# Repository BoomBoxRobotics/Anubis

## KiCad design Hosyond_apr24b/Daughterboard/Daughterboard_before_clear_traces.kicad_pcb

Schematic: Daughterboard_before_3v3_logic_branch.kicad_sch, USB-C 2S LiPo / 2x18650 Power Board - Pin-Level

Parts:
BT1: 18650 Cell 1 lower
BT2: 18650 Cell 2 upper
C1: 10uF 10V X5R; C_0805_2012Metric
C2, C8, C17, C19, C27, C29: 100nF 10V X7R; C_0603_1608Metric
C3, C5: 22uF 16V X5R; C_0805_2012Metric
C4, C7, C9, C10, C12, C15, C21, C24, C25, C26: 100nF 16V X7R; C_0603_1608Metric
C6: 4.7uF 6.3V X5R; C_0603_1608Metric
C11, C16: 10uF 16V X5R; C_0805_2012Metric
C13, C14, C22, C23: 22uF 10V X5R; C_0805_2012Metric
C18, C20, C28: 1uF 10V X5R; C_0603_1608Metric
D1: 5V VBUS TVS; D_SOD-323
D2: LED green; LED_0603_1608Metric
D3: LED blue; LED_0603_1608Metric
D4, D5, D6, D7: 4ch 3.3V GPIO TVS array TBD; SOT-23-6_NoPad6
F1: 2A hold polyfuse; Fuse_1206_3216Metric
F2: PTC/fuse cell1; Fuse_1206_3216Metric
F3: PTC/fuse cell2; Fuse_1206_3216Metric
F4: 2A system fuse; Fuse_1206_3216Metric
J1: USB-C 5V Sink; USB_C_Receptacle_GCT_USB4125-xx-x_6P_TopMnt_Horizontal
J2: Switched power outputs
J4: UART JST-GH 1.25mm; JST_GH_SM05B-GHS-TB_1x05-1MP_P1.25mm_Horizontal
J5: I2C male header 2.54mm; PinHeader_1x04_P2.54mm_Vertical
J6: Deep sleep pushbutton header; PinHeader_1x02_P2.54mm_Vertical
J7: 2S balance input JST-XH; JST_XH_B3B-XH-A_1x03_P2.50mm_Vertical
J8: Analog input header; PinHeader_1x10_P2.54mm_Vertical
J30: J3P Hosyond +5V_SW solder pad; TestPoint_Pad_1.5x1.5mm
J31: J3A Hosyond UART_TX solder pad; TestPoint_Pad_1.5x1.5mm
J32: J3B Hosyond UART_RX solder pad; TestPoint_Pad_1.5x1.5mm
J33: J3C Hosyond I2C_SDA solder pad; TestPoint_Pad_1.5x1.5mm
J34: J3D Hosyond I2C_SCL solder pad; TestPoint_Pad_1.5x1.5mm
J35: J3E Hosyond GPIO2 solder pad; TestPoint_Pad_1.5x1.5mm
J36: J3F Hosyond GPIO3 solder pad; TestPoint_Pad_1.5x1.5mm
J37: J3G Hosyond GPIO14 solder pad; TestPoint_Pad_1.5x1.5mm
J38: J3H Hosyond GPIO21 solder pad; TestPoint_Pad_1.5x1.5mm
J39: J3I Hosyond GND solder pad; TestPoint_Pad_1.5x1.5mm
J91: MCP23017 GPA0 solder pad; TestPoint_Pad_1.5x1.5mm
J92: MCP23017 GPA1 solder pad; TestPoint_Pad_1.5x1.5mm
J93: MCP23017 GPA2 solder pad; TestPoint_Pad_1.5x1.5mm
J94: MCP23017 GPA3 solder pad; TestPoint_Pad_1.5x1.5mm
J95: MCP23017 GPA4 solder pad; TestPoint_Pad_1.5x1.5mm
J96: MCP23017 GPA5 solder pad; TestPoint_Pad_1.5x1.5mm
J97: MCP23017 GPA6 solder pad; TestPoint_Pad_1.5x1.5mm
J98: MCP23017 GPA7 solder pad; TestPoint_Pad_1.5x1.5mm
J99: MCP23017 GPB0 solder pad; TestPoint_Pad_1.5x1.5mm
J910: MCP23017 GPB1 solder pad; TestPoint_Pad_1.5x1.5mm
J911: MCP23017 GPB2 solder pad; TestPoint_Pad_1.5x1.5mm
J912: MCP23017 GPB3 solder pad; TestPoint_Pad_1.5x1.5mm
J913: MCP23017 GPB4 solder pad; TestPoint_Pad_1.5x1.5mm
J914: MCP23017 GPB5 solder pad; TestPoint_Pad_1.5x1.5mm
J915: MCP23017 GPB6 solder pad; TestPoint_Pad_1.5x1.5mm
J916: MCP23017 GPB7 solder pad; TestPoint_Pad_1.5x1.5mm
J925: MCP23017 INTA solder pad; TestPoint_Pad_1.5x1.5mm
J926: MCP23017 INTB solder pad; TestPoint_Pad_1.5x1.5mm
J927: MCP23017 RESET solder pad; TestPoint_Pad_1.5x1.5mm
J928: MCP23017 +3V3_SW solder pad; TestPoint_Pad_1.5x1.5mm
J929: MCP23017 GND solder pad; TestPoint_Pad_1.5x1.5mm
L1: 4.7uH >=3A sat; L_APV_ANR4020
L2: 4.7uH >=2A sat; L_APV_ANR4020
L3: 1uH >=4A sat; L_APV_ANR5040
Q1: CSD83325L; CSD83325L_YJE0006A
R1, R2: 5.1k 1%; R_0603_1608Metric
R3: 806R 1% TBD; R_0603_1608Metric
R4: TBD 1%; R_0603_1608Metric
R5: 10k 1%; R_0603_1608Metric
R6, R7: 2.2k; R_0603_1608Metric
R8: 523k 1%; R_0603_1608Metric
R9, R12: 100k 1%; R_0603_1608Metric
R10, R13: 100k; R_0603_1608Metric
R11: 316k 1%; R_0603_1608Metric
R14, R15: 470R 1%; R_0603_1608Metric
R16: 2.0k 1%; R_0603_1608Metric
R17, R18: 330R; R_0603_1608Metric
R19, R20: 4.7k; R_0603_1608Metric
R21, R22, R23, R24, R25, R26, R27, R28, R29, R30, R31, R32, R33, R34, R35, R36, R37, R38: 100R; R_0603_1608Metric
R39, R40, R41: 0R; R_0603_1608Metric
R42, R43, R44: 10k; R_0603_1608Metric
SW1: Pololu #2808 5V switch; Pololu_2808_Raised_Header
SW2: Pololu #2808 3V3 switch; Pololu_2808_Raised_Header
TH1: 10k NTC; R_0603_1608Metric
TP1: USB_VBUS test pad; TestPoint_Pad_D1.0mm
TP2: CHG_IN test pad; TestPoint_Pad_D1.0mm
TP3: PACK_P test pad; TestPoint_Pad_D1.0mm
TP4: CELL_MID test pad; TestPoint_Pad_D1.0mm
TP5: BAT_SYS test pad; TestPoint_Pad_D1.0mm
TP6: +5V test pad; TestPoint_Pad_D1.0mm
TP7: +3V3 test pad; TestPoint_Pad_D1.0mm
TP8: +5V_SW test pad; TestPoint_Pad_D1.0mm
TP9: +3V3_SW test pad; TestPoint_Pad_D1.0mm
TP10: CHG_STAT test pad; TestPoint_Pad_D1.0mm
TP11: PG_STAT test pad; TestPoint_Pad_D1.0mm
TP12: BATT_RAW_N test pad; TestPoint_Pad_D1.0mm
TP13: VM_SENSE test pad; TestPoint_Pad_D1.0mm
TP14: GND test pad; TestPoint_Pad_D1.0mm
U1: BQ25887RGE 2S charger; Texas_RGE0024H_VQFN-24-1EP_4x4mm_P0.5mm_EP2.7x2.7mm
U2: S-8252AAH-M6T1U; SOT-23-6
U3: AP63200WU 5V Buck; TSOT-23-6
U4: AP63200WU 3V3 Buck; TSOT-23-6
U5: ADS1115IDGS 0x48; TSSOP-10_3x3mm_P0.5mm
U6: ADS1115IDGS 0x49; TSSOP-10_3x3mm_P0.5mm
U7: MCP23017-E/SO; SOIC-28W_7.5x17.9mm_P1.27mm_NoPads11_14

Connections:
+3V3: C22.1, C23.1, L2.2, R11.1, SW2.1 (VIN), TP7.1
+5V: C13.1, C14.1, L1.2, R8.1, SW1.1 (VIN), TP6.1
+5V_SW: J2.1, J4.1, J30.1, SW1.2 (VOUT), TP8.1
AIN0: J8.1, U5.4 (AIN0)
AIN1: J8.2, U5.5 (AIN1)
AIN2: J8.3, U5.6 (AIN2)
AIN3: J8.4, U5.7 (AIN3)
AIN4: J8.5, U6.4 (AIN0)
AIN5: J8.6, U6.5 (AIN1)
AIN6: J8.7, U6.6 (AIN2)
AIN7: J8.8, U6.7 (AIN3)
BATT_RAW_N: BT1.2, C10.2, C26.2, J7.1, Q1.A1 (S1A), Q1.C1 (S1B), TP12.1, U2.6 (VSS)
BAT_SYS: C11.1, C12.1, C16.1, C21.1, F4.2, R10.2, R13.2, TP5.1, U3.3 (IN), U4.3 (IN)
BST_3V3: C24.1, U4.6 (BST)
BST_5V: C15.1, U3.6 (BST)
BTST: C7.1, U1.12 (BTST)
CBSET: C8.1, R4.1, U1.10 (CBSET)
CC1: J1.A5 (CC1), R1.1
CC2: J1.B5 (CC2), R2.1
CELL1_P: BT1.1, F2.1
CELL2_P: BT2.1, F3.1
CHG_IN: C1.1, C2.1, D1.1, F1.2, TP2.1, U1.23 (VBUS)
CHG_STAT: D2.2, TP10.1, U1.2 (STAT)
CHG_SW: C7.2, L3.2, U1.17 (SW1), U1.18 (SW2)
CO_GATE: Q1.B2 (G2), R22.2
CTRL_3V3_SW: R18.2, SW2.4 (CTRL)
CTRL_5V_SW: R17.2, SW1.4 (CTRL)
DO_GATE: Q1.B1 (G1), R21.2
EN_3V3: R13.1, U4.2 (EN)
EN_5V: R10.1, U3.2 (EN)
EXP_GPA0: D4.1 (IO1), J91.1, R23.2
EXP_GPA1: D4.2 (IO2), J92.1, R24.2
EXP_GPA2: D4.4 (IO3), J93.1, R25.2
EXP_GPA3: D4.5 (IO4), J94.1, R26.2
EXP_GPA4: D5.1 (IO1), J95.1, R27.2
EXP_GPA5: D5.2 (IO2), J96.1, R28.2
EXP_GPA6: D5.4 (IO3), J97.1, R29.2
EXP_GPA7: D5.5 (IO4), J98.1, R30.2
EXP_GPB0: D6.1 (IO1), J99.1, R31.2
EXP_GPB1: D6.2 (IO2), J910.1, R32.2
EXP_GPB2: D6.4 (IO3), J911.1, R33.2
EXP_GPB3: D6.5 (IO4), J912.1, R34.2
EXP_GPB4: D7.1 (IO1), J913.1, R35.2
EXP_GPB5: D7.2 (IO2), J914.1, R36.2
EXP_GPB6: D7.4 (IO3), J915.1, R37.2
EXP_GPB7: D7.5 (IO4), J916.1, R38.2
FB_3V3: R11.2, R12.1, U4.1 (FB)
FB_5V: R8.2, R9.1, U3.1 (FB)
GPIO2: J35.1, R17.1
GPIO3: J36.1, R18.1
GPIO14: J6.1, J37.1
GPIO21: J6.2, J38.1
I2C_SCL: J5.4, J34.1, R20.1, U1.5 (SCL), U5.10 (SCL), U6.10 (SCL), U7.12 (SCL)
I2C_SDA: J5.3, J33.1, R19.1, U1.4 (SDA), U5.9 (SDA), U6.9 (SDA), U7.13 (SDA)
ILIM: R3.1, U1.8 (ILIM)
LED_CHG_A: D2.1, R6.2
LED_PGOOD_A: D3.1, R7.2
MCP_A0: R39.1, U7.15 (A0)
MCP_A1: R40.1, U7.16 (A1)
MCP_A2: R41.1, U7.17 (A2)
MCP_GPA0: R23.1, U7.21 (GPA0)
MCP_GPA1: R24.1, U7.22 (GPA1)
MCP_GPA2: R25.1, U7.23 (GPA2)
MCP_GPA3: R26.1, U7.24 (GPA3)
MCP_GPA4: R27.1, U7.25 (GPA4)
MCP_GPA5: R28.1, U7.26 (GPA5)
MCP_GPA6: R29.1, U7.27 (GPA6)
MCP_GPA7: R30.1, U7.28 (GPA7)
MCP_GPB0: R31.1, U7.1 (GPB0)
MCP_GPB1: R32.1, U7.2 (GPB1)
MCP_GPB2: R33.1, U7.3 (GPB2)
MCP_GPB3: R34.1, U7.4 (GPB3)
MCP_GPB4: R35.1, U7.5 (GPB4)
MCP_GPB5: R36.1, U7.6 (GPB5)
MCP_GPB6: R37.1, U7.7 (GPB6)
MCP_GPB7: R38.1, U7.8 (GPB7)
MCP_INTA: J925.1, R43.2, U7.20 (INTA)
MCP_INTB: J926.1, R44.2, U7.19 (INTB)
MCP_RESET: C29.1, J927.1, R42.2, U7.18 (~RESET)
PACK_P: C5.1, C9.1, F3.2, F4.1, J7.3, R14.1, TP3.1, U1.13 (BAT1), U1.14 (BAT2), U1.15 (SNS1), U1.16 (SNS2)
PG_STAT: D3.2, TP11.1, U1.1 (~PG)
PMID: C3.1, C4.1, L3.1, U1.21 (PMID1), U1.22 (PMID2)
PROT_VC: C25.2, C26.1, R15.2, U2.4 (VC)
PROT_VDD: C25.1, R14.2, U2.5 (VDD)
REGN: C6.1, R5.1, R6.1, R7.1, U1.11 (REGN)
S8252_CO: R22.1, U2.2 (CO)
S8252_DO: R21.1, U2.1 (DO)
SW_3V3: C24.2, L2.1, U4.5 (SW)
SW_5V: C15.2, L1.1, U3.5 (SW)
TS: R5.2, TH1.1, U1.7 (TS)
UART_RX: J4.4, J32.1
UART_TX: J4.3, J31.1
USB_VBUS: F1.1, J1.A9 (VBUS_A), J1.B9 (VBUS_B), TP1.1
VM_SENSE: R16.1, TP13.1, U2.3 (VM)

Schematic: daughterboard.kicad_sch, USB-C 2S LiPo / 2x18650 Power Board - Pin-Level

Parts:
BT1: 18650 Cell 1 lower
BT2: 18650 Cell 2 upper
C1: 10uF 10V X5R; C_0805_2012Metric
C2, C19, C27, C29: 100nF 10V X7R; C_0603_1608Metric
C3, C5: 22uF 16V X5R; C_0805_2012Metric
C4, C7, C9, C10, C12, C15, C21, C24, C25, C26: 100nF 16V X7R; C_0603_1608Metric
C6: 4.7uF 6.3V X5R; C_0603_1608Metric
C8: 100nF 10V X7R; C_0603_1608Metric; not fitted
C11, C16: 10uF 16V X5R; C_0805_2012Metric
C13, C14, C22, C23: 22uF 10V X5R; C_0805_2012Metric
C17: 100nF 10V X7R DNP; C_0603_1608Metric
C18, C20, C28: 1uF 10V X5R; C_0603_1608Metric
D1: 5V VBUS TVS; D_SOD-323
D2: LED green; LED_0603_1608Metric
D3: LED blue; LED_0603_1608Metric
D4, D5, D6, D7: SP0504BAHTG 4ch GPIO TVS; SOT-23-6_NoPad6
F1: 2A hold polyfuse; Fuse_1206_3216Metric
F2: PTC/fuse cell1; Fuse_1206_3216Metric
F3: PTC/fuse cell2; Fuse_1206_3216Metric
F4: 2A system fuse; Fuse_1206_3216Metric
J1: USB-C 5V Sink; USB_C_Receptacle_GCT_USB4125-xx-x_6P_TopMnt_Horizontal
J2: Switched power outputs
J4: UART JST-GH 1.25mm; JST_GH_SM05B-GHS-TB_1x05-1MP_P1.25mm_Horizontal
J5: I2C male header 2.54mm; PinHeader_1x04_P2.54mm_Vertical
J6: Deep sleep pushbutton header; PinHeader_1x02_P2.54mm_Vertical
J7: 2S balance input JST-XH; JST_XH_B3B-XH-A_1x03_P2.50mm_Vertical
J8: Analog input header; PinHeader_1x10_P2.54mm_Vertical
J30: J3P Hosyond +5V_SW solder pad; TestPoint_Pad_1.5x1.5mm
J31: J3A Hosyond UART_TX solder pad; TestPoint_Pad_1.5x1.5mm
J32: J3B Hosyond UART_RX solder pad; TestPoint_Pad_1.5x1.5mm
J33: J3C Hosyond I2C_SDA solder pad; TestPoint_Pad_1.5x1.5mm
J34: J3D Hosyond I2C_SCL solder pad; TestPoint_Pad_1.5x1.5mm
J35: J3E Hosyond GPIO2 solder pad; TestPoint_Pad_1.5x1.5mm
J36: J3F Hosyond GPIO3 solder pad; TestPoint_Pad_1.5x1.5mm
J37: J3G Hosyond GPIO14 solder pad; TestPoint_Pad_1.5x1.5mm
J38: J3H Hosyond GPIO21 solder pad; TestPoint_Pad_1.5x1.5mm
J39: J3I Hosyond GND solder pad; TestPoint_Pad_1.5x1.5mm
J91: MCP23017 GPA0 solder pad; TestPoint_Pad_1.5x1.5mm
J92: MCP23017 GPA1 solder pad; TestPoint_Pad_1.5x1.5mm
J93: MCP23017 GPA2 solder pad; TestPoint_Pad_1.5x1.5mm
J94: MCP23017 GPA3 solder pad; TestPoint_Pad_1.5x1.5mm
J95: MCP23017 GPA4 solder pad; TestPoint_Pad_1.5x1.5mm
J96: MCP23017 GPA5 solder pad; TestPoint_Pad_1.5x1.5mm
J97: MCP23017 GPA6 solder pad; TestPoint_Pad_1.5x1.5mm
J98: MCP23017 GPA7 solder pad; TestPoint_Pad_1.5x1.5mm
J99: MCP23017 GPB0 solder pad; TestPoint_Pad_1.5x1.5mm
J910: MCP23017 GPB1 solder pad; TestPoint_Pad_1.5x1.5mm
J911: MCP23017 GPB2 solder pad; TestPoint_Pad_1.5x1.5mm
J912: MCP23017 GPB3 solder pad; TestPoint_Pad_1.5x1.5mm
J913: MCP23017 GPB4 solder pad; TestPoint_Pad_1.5x1.5mm
J914: MCP23017 GPB5 solder pad; TestPoint_Pad_1.5x1.5mm
J915: MCP23017 GPB6 solder pad; TestPoint_Pad_1.5x1.5mm
J916: MCP23017 GPB7 solder pad; TestPoint_Pad_1.5x1.5mm
J925: MCP23017 INTA solder pad; TestPoint_Pad_1.5x1.5mm
J926: MCP23017 INTB solder pad; TestPoint_Pad_1.5x1.5mm
J927: MCP23017 RESET solder pad; TestPoint_Pad_1.5x1.5mm
J928: MCP23017 +3V3_SW solder pad; TestPoint_Pad_1.5x1.5mm
J929: MCP23017 GND solder pad; TestPoint_Pad_1.5x1.5mm
L1: 4.7uH >=3A sat; L_APV_ANR4020
L2: 4.7uH >=2A sat; L_APV_ANR4020
L3: 1uH >=4A sat; L_APV_ANR5040
Q1: CSD83325L; CSD83325L_YJE0006A
R1, R2: 5.1k 1%; R_0603_1608Metric
R3: 806R 1% ILIM; R_0603_1608Metric
R4: 220R 1% CBSET; R_0603_1608Metric
R5: 10k 1%; R_0603_1608Metric
R6, R7: 2.2k; R_0603_1608Metric
R8: 523k 1%; R_0603_1608Metric
R9, R12: 100k 1%; R_0603_1608Metric
R10, R13: 100k; R_0603_1608Metric
R11: 316k 1%; R_0603_1608Metric
R14, R15: 470R 1%; R_0603_1608Metric
R16: 2.0k 1%; R_0603_1608Metric
R17, R18: 330R; R_0603_1608Metric
R19, R20: 4.7k; R_0603_1608Metric
R21, R22, R23, R24, R25, R26, R27, R28, R29, R30, R31, R32, R33, R34, R35, R36, R37, R38: 100R; R_0603_1608Metric
R39, R40, R41, R45: 0R; R_0603_1608Metric
R42, R43, R44: 10k; R_0603_1608Metric
SW1: Pololu #2808 5V switch; Pololu_2808_Raised_Header
SW2: Pololu #2808 3V3 switch; Pololu_2808_Raised_Header
TH1: 10k NTC; R_0603_1608Metric
TP1: USB_VBUS test pad; TestPoint_Pad_D1.0mm
TP2: CHG_IN test pad; TestPoint_Pad_D1.0mm
TP3: PACK_P test pad; TestPoint_Pad_D1.0mm
TP4: CELL_MID test pad; TestPoint_Pad_D1.0mm
TP5: BAT_SYS test pad; TestPoint_Pad_D1.0mm
TP6: +5V test pad; TestPoint_Pad_D1.0mm
TP7: +3V3 test pad; TestPoint_Pad_D1.0mm
TP8: +5V_SW test pad; TestPoint_Pad_D1.0mm
TP9: +3V3_SW test pad; TestPoint_Pad_D1.0mm
TP10: CHG_STAT test pad; TestPoint_Pad_D1.0mm
TP11: PG_STAT test pad; TestPoint_Pad_D1.0mm
TP12: BATT_RAW_N test pad; TestPoint_Pad_D1.0mm
TP13: VM_SENSE test pad; TestPoint_Pad_D1.0mm
TP14: GND test pad; TestPoint_Pad_D1.0mm
U1: BQ25887RGE 2S charger; Texas_RGE0024H_VQFN-24-1EP_4x4mm_P0.5mm_EP2.7x2.7mm
U2: S-8252AAH-M6T1U; SOT-23-6
U3: AP63200WU 5V Buck; TSOT-23-6
U4: AP63200WU 3V3 Buck; TSOT-23-6
U5: ADS1115IDGS 0x48; TSSOP-10_3x3mm_P0.5mm
U6: ADS1115IDGS 0x49; TSSOP-10_3x3mm_P0.5mm
U7: MCP23017-E/SO; SOIC-28W_7.5x17.9mm_P1.27mm_NoPads11_14

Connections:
+3V3: C22.1, C23.1, L2.2, R11.1, SW2.1 (VIN), TP7.1
+5V: C13.1, C14.1, L1.2, R8.1, SW1.1 (VIN), TP6.1
+5V_SW: J2.1, J4.1, J30.1, SW1.2 (VOUT), TP8.1
AIN0: J8.1, U5.4 (AIN0)
AIN1: J8.2, U5.5 (AIN1)
AIN2: J8.3, U5.6 (AIN2)
AIN3: J8.4, U5.7 (AIN3)
AIN4: J8.5, U6.4 (AIN0)
AIN5: J8.6, U6.5 (AIN1)
AIN6: J8.7, U6.6 (AIN2)
AIN7: J8.8, U6.7 (AIN3)
BATT_RAW_N: BT1.2, C10.2, C26.2, J7.1, Q1.A1 (S1A), Q1.C1 (S1B), TP12.1, U2.6 (VSS)
BAT_SYS: C11.1, C12.1, C16.1, C21.1, F4.2, R10.2, R13.2, TP5.1, U3.3 (IN), U4.3 (IN)
BST_3V3: C24.1, U4.6 (BST)
BST_5V: C15.1, U3.6 (BST)
BTST: C7.1, U1.12 (BTST)
CBSET: C8.1, R4.1, U1.10 (CBSET)
CC1: J1.A5 (CC1), R1.1
CC2: J1.B5 (CC2), R2.1
CELL1_P: BT1.1, F2.1
CELL2_P: BT2.1, F3.1
CHG_IN: C1.1, C2.1, D1.1, F1.2, TP2.1, U1.23 (VBUS)
CHG_STAT: D2.2, TP10.1, U1.2 (STAT)
CHG_SW: C7.2, L3.2, U1.17 (SW1), U1.18 (SW2)
CO_GATE: Q1.B2 (G2), R22.2
CTRL_3V3_SW: R18.2, SW2.4 (CTRL)
CTRL_5V_SW: R17.2, SW1.4 (CTRL)
DO_GATE: Q1.B1 (G1), R21.2
EN_3V3: R13.1, U4.2 (EN)
EN_5V: R10.1, U3.2 (EN)
EXP_GPA0: D4.1 (IO1), J91.1, R23.2
EXP_GPA1: D4.2 (IO2), J92.1, R24.2
EXP_GPA2: D4.4 (IO3), J93.1, R25.2
EXP_GPA3: D4.5 (IO4), J94.1, R26.2
EXP_GPA4: D5.1 (IO1), J95.1, R27.2
EXP_GPA5: D5.2 (IO2), J96.1, R28.2
EXP_GPA6: D5.4 (IO3), J97.1, R29.2
EXP_GPA7: D5.5 (IO4), J98.1, R30.2
EXP_GPB0: D6.1 (IO1), J99.1, R31.2
EXP_GPB1: D6.2 (IO2), J910.1, R32.2
EXP_GPB2: D6.4 (IO3), J911.1, R33.2
EXP_GPB3: D6.5 (IO4), J912.1, R34.2
EXP_GPB4: D7.1 (IO1), J913.1, R35.2
EXP_GPB5: D7.2 (IO2), J914.1, R36.2
EXP_GPB6: D7.4 (IO3), J915.1, R37.2
EXP_GPB7: D7.5 (IO4), J916.1, R38.2
FB_3V3: R11.2, R12.1, U4.1 (FB)
FB_5V: R8.2, R9.1, U3.1 (FB)
GPIO2: J35.1, R17.1
GPIO3: J36.1, R18.1
GPIO14: J6.1, J37.1
GPIO21: J6.2, J38.1
I2C_SCL: J5.4, J34.1, R20.1, U1.5 (SCL), U5.10 (SCL), U6.10 (SCL), U7.12 (SCL)
I2C_SDA: J5.3, J33.1, R19.1, U1.4 (SDA), U5.9 (SDA), U6.9 (SDA), U7.13 (SDA)
ILIM: R3.1, U1.8 (ILIM)
LED_CHG_A: D2.1, R6.2
LED_PGOOD_A: D3.1, R7.2
MCP_A0: R39.1, U7.15 (A0)
MCP_A1: R40.1, U7.16 (A1)
MCP_A2: R41.1, U7.17 (A2)
MCP_GPA0: R23.1, U7.21 (GPA0)
MCP_GPA1: R24.1, U7.22 (GPA1)
MCP_GPA2: R25.1, U7.23 (GPA2)
MCP_GPA3: R26.1, U7.24 (GPA3)
MCP_GPA4: R27.1, U7.25 (GPA4)
MCP_GPA5: R28.1, U7.26 (GPA5)
MCP_GPA6: R29.1, U7.27 (GPA6)
MCP_GPA7: R30.1, U7.28 (GPA7)
MCP_GPB0: R31.1, U7.1 (GPB0)
MCP_GPB1: R32.1, U7.2 (GPB1)
MCP_GPB2: R33.1, U7.3 (GPB2)
MCP_GPB3: R34.1, U7.4 (GPB3)
MCP_GPB4: R35.1, U7.5 (GPB4)
MCP_GPB5: R36.1, U7.6 (GPB5)
MCP_GPB6: R37.1, U7.7 (GPB6)
MCP_GPB7: R38.1, U7.8 (GPB7)
MCP_INTA: J925.1, R43.2, U7.20 (INTA)
MCP_INTB: J926.1, R44.2, U7.19 (INTB)
MCP_RESET: C29.1, J927.1, R42.2, U7.18 (~RESET)
PACK_P: C5.1, C9.1, F3.2, F4.1, J7.3, R14.1, TP3.1, U1.13 (BAT1), U1.14 (BAT2), U1.15 (SNS1), U1.16 (SNS2)
PG_STAT: D3.2, TP11.1, U1.1 (~PG)
PMID: C3.1, C4.1, L3.1, U1.21 (PMID1), U1.22 (PMID2)
PROT_VC: C25.2, C26.1, R15.2, U2.4 (VC)
PROT_VDD: C25.1, R14.2, U2.5 (VDD)
REGN: C6.1, R5.1, R6.1, R7.1, U1.11 (REGN)
S8252_CO: R22.1, U2.2 (CO)
S8252_DO: R21.1, U2.1 (DO)
SW_3V3: C24.2, L2.1, U4.5 (SW)
SW_5V: C15.2, L1.1, U3.5 (SW)
TS: R5.2, TH1.1, U1.7 (TS)
UART_RX: J4.4, J32.1
UART_TX: J4.3, J31.1
USB_VBUS: F1.1, J1.A9 (VBUS_A), J1.B9 (VBUS_B), TP1.1
VM_SENSE: R16.1, TP13.1, U2.3 (VM)

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
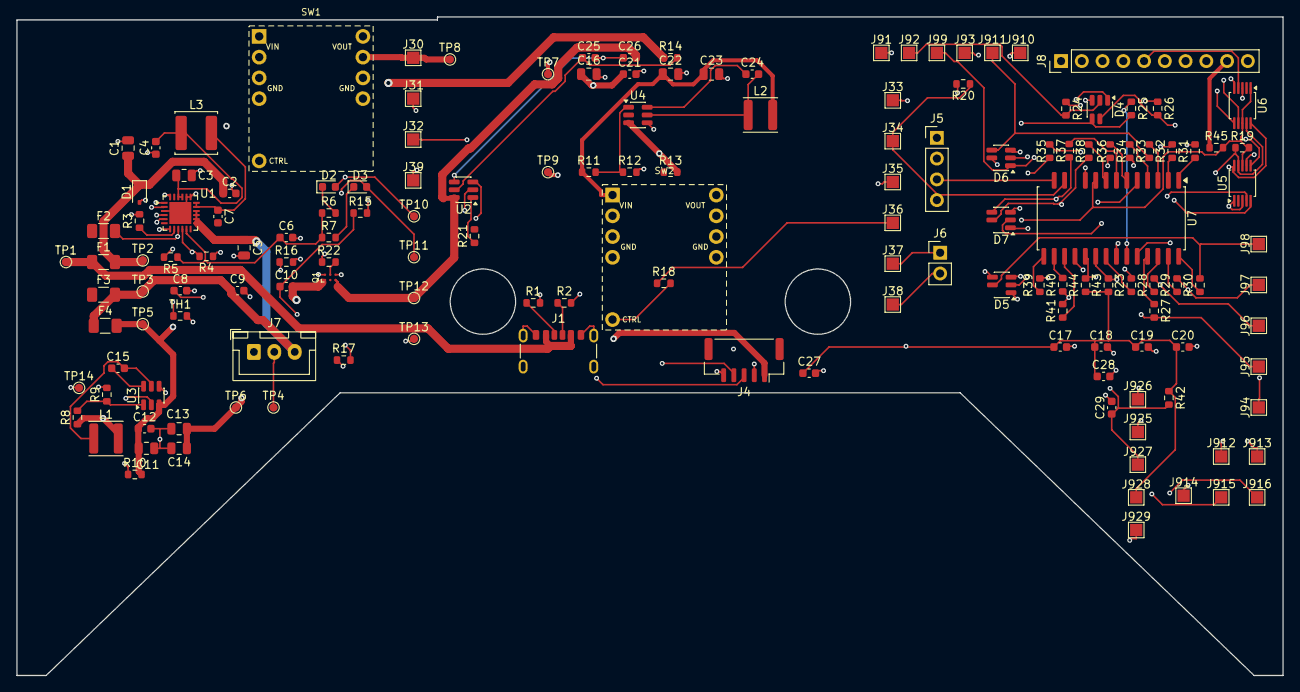
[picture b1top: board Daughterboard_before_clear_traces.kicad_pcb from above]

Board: 4 copper layers, 155.0 x 80.6 mm, 150 parts (0 on the bottom side), 96 nets.

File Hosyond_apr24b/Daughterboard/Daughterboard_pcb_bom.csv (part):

"Refs","Value","Footprint","Qty","Description","Datasheet","Purchase Link","DNP"
"BT1","18650 Cell 1 lower","","1","","","https://www.digikey.com/en/products/result?keywords=18650+ba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",""
"BT2","18650 Cell 2 upper","","1","","","https://www.digikey.com/en/products/result?keywords=18650+ba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",""
"C1","10uF 10V X5R","Capacitor_SMD:C_0805_2012Metric","1","","","https://www.digikey.com/en/products/result?keywords=10uF+10V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",""
"C2,C19,C27,C29","100nF 10V X7R","Capacitor_SMD:C_0603_1608Metric","4","","","https://www.digikey.com/en/products/result?keywords=100nF+10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",""
"C3,C5","22uF 16V X5R","Capacitor_SMD:C_0805_2012Metric","2","","","https://www.digikey.com/en/products/result?keywords=22uF+16V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",""
"C4,C7,C9,C10,C12,C15,C21,C24-C26","100nF 16V X7R","Capacitor_SMD:C_0603_1608Metric","10","","","https://www.digikey.com/en/products/result?keywords=100nF+16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",""
"C6","4.7uF 6.3V X5R","Capacitor_SMD:C_0603_1608Metric","1","","","https://www.digikey.com/en/products/result?keywords=4.7uF+6.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",""
"C11,C16","10uF 16V X5R","Capacitor_SMD:C_0805_2012Metric","2","","","https://www.digikey.com/en/products/result?keywords=10uF+16V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",""
"C13,C14,C22,C23","22uF 10V X5R","Capacitor_SMD:C_0805_2012Metric","4","","","https://www.digikey.com/en/products/result?keywords=22uF+10V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",""
"C17","100nF 10V X7R DNP","Capacitor_SMD:C_0603_1608Metric","1","","","https://www.digikey.com/en/products/result?keywords=100nF+10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",""
"C18,C20,C28","1uF 10V X5R","Capacitor_SMD:C_0603_1608Metric","3","","","https://www.digikey.com/en/products/result?keywords=1uF+10V+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",""
"D1","5V VBUS TVS","Diode_SMD:D_SOD-323","1","","","https://www.digikey.com/en/products/result?keywords=5V+VBUS+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",""
"D2","LED green","LED_SMD:LED_0603_1608Metric","1","","","https://www.digikey.com/en/products/result?keywords=LED+gree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",""
"D3","LED blue","LED_SMD:LED_0603_1608Metric","1","","","https://www.digikey.com/en/products/result?keywords=LED+blue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",""
"D4-D7","SP0504BAHTG 4ch GPIO TVS","Daughterboard:SOT-23-6_NoPad6","4","","https://www.littelfuse.com/products/tvs-diode-arrays/low-cap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","https://www.digikey.com/en/products/result?keywords=SP0504BAHTG",""
"F1","2A hold polyfuse","Fuse:Fuse_1206_3216Metric","1","","","https://www.digikey.com/en/products/result?keywords=2A+hold+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",""
"F2","PTC/fuse cell1","Fuse:Fuse_1206_3216Metric","1","","","https://www.digikey.com/en/products/result?keywords=PTC%2Ffu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",""
"F3","PTC/fuse cell2","Fuse:Fuse_1206_3216Metric","1","","","https://www.digikey.com/en/products/result?keywords=PTC%2Ffu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",""
"F4","2A system fuse","Fuse:Fuse_1206_3216Metric","1","","","https://www.digikey.com/en/products/result?keywords=2A+syste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",""
"J1","USB-C 5V Sink","Connector_USB:USB_C_Receptacle_GCT_USB4125-xx-x_6P_TopMnt_Horizontal","1","","","https://www.digikey.com/en/products/result?keywords=GCT+USB4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",""
"J2","Switched power outputs","","1","","","https://www.digikey.com/en/products/result?keywords=2.54mm+p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",""
"J4","UART JST-GH 1.25mm","Connector_JST:JST_GH_SM05B-GHS-TB_1x05-1MP_P1.25mm_Horizontal","1","","","https://www.digikey.com/en/products/result?keywords=SM05B-GH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",""
"J5","I2C male header 2.54mm","Connector_PinHeader_2.54mm:PinHeader_1x04_P2.54mm_Vertical","1","","","https://www.digikey.com/en/products/result?keywords=2.54mm+p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",""
"J6","Deep sleep pushbutton header","Connector_PinHeader_2.54mm:PinHeader_1x02_P2.54mm_Vertical","1","","","https://www.digikey.com/en/products/result?keywords=2.54mm+p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",""
"J7","2S balance input JST-XH","Connector_JST:JST_XH_B3B-XH-A_1x03_P2.50mm_Vertical","1","","","https://www.digikey.com/en/products/result?keywords=JST+XH+3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",""
"J8","Analog input header","Connector_PinHeader_2.54mm:PinHeader_1x10_P2.54mm_Vertical","1","","","https://www.digikey.com/en/products/result?keywords=2.54mm+p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",""
"J30","J3P Hosyond +5V_SW solder pad","TestPoint:TestPoint_Pad_1.5x1.5mm","1","","","",""
"J31","J3A Hosyond UART_TX solder pad","TestPoint:TestPoint_Pad_1.5x1.5mm","1","","","",""
"J32","J3B Hosyond UART_RX solder pad","TestPoint:TestPoint_Pad_1.5x1.5mm","1","","","",""
"J33","J3C Hosyond I2C_SDA solder pad","TestPoint:TestPoint_Pad_1.5x1.5mm","1","","","",""
"J34","J3D Hosyond I2C_SCL solder pad","TestPoint:TestPoint_Pad_1.5x1.5mm","1","","","",""
"J35","J3E Hosyond GPIO2 solder pad","TestPoint:TestPoint_Pad_1.5x1.5mm","1","","","",""
"J36","J3F Hosyond GPIO3 solder pad","TestPoint:TestPoint_Pad_1.5x1.5mm","1","","","",""
"J37","J3G Hosyond GPIO14 solder pad","TestPoint:TestPoint_Pad_1.5x1.5mm","1","","","",""
"J38","J3H Hosyond GPIO21 solder pad","TestPoint:TestPoint_Pad_1.5x1.5mm","1","","","",""
"J39","J3I Hosyond GND solder pad","TestPoint:TestPoint_Pad_1.5x1.5mm","1","","","",""
"J91","MCP23017 GPA0 solder pad","TestPoint:TestPoint_Pad_1.5x1.5mm","1","","","",""
"J92","MCP23017 GPA1 solder pad","TestPoint:TestPoint_Pad_1.5x1.5mm","1","","","",""
"J93","MCP23017 GPA2 solder pad","TestPoint:TestPoint_Pad_1.5x1.5mm","1","","","",""
"J94","MCP23017 GPA3 solder pad","TestPoint:TestPoint_Pad_1.5x1.5mm","1","","","",""
"J95","MCP23017 GPA4 solder pad","TestPoint:TestPoint_Pad_1.5x1.5mm","1","","","",""
"J96","MCP23017 GPA5 solder pad","TestPoint:TestPoint_Pad_1.5x1.5mm","1","","","",""
"J97","MCP23017 GPA6 solder pad","TestPoint:TestPoint_Pad_1.5x1.5mm","1","","","",""
"J98","MCP23017 GPA7 solder pad","TestPoint:TestPoint_Pad_1.5x1.5mm","1","","","",""
"J99","MCP23017 GPB0 solder pad","TestPoint:TestPoint_Pad_1.5x1.5mm","1","","","",""
"J910","MCP23017 GPB1 solder pad","TestPoint:TestPoint_Pad_1.5x1.5mm","1","","","",""
"J911","MCP23017 GPB2 solder pad","TestPoint:TestPoint_Pad_1.5x1.5mm","1","","","",""
"J912","MCP23017 GPB3 solder pad","TestPoint:TestPoint_Pad_1.5x1.5mm","1","","","",""
"J913","MCP23017 GPB4 solder pad","TestPoint:TestPoint_Pad_1.5x1.5mm","1","","","",""
"J914","MCP23017 GPB5 solder pad","TestPoint:TestPoint_Pad_1.5x1.5mm","1","","","",""
"J915","MCP23017 GPB6 solder pad","TestPoint:TestPoint_Pad_1.5x1.5mm","1","","","",""
"J916","MCP23017 GPB7 solder pad","TestPoint:TestPoint_Pad_1.5x1.5mm","1","","","",""
"J925","MCP23017 INTA solder pad","TestPoint:TestPoint_Pad_1.5x1.5mm","1","","","",""
"J926","MCP23017 INTB solder pad","TestPoint:TestPoint_Pad_1.5x1.5mm","1","","","",""
"J927","MCP23017 RESET solder pad","TestPoint:TestPoint_Pad_1.5x1.5mm","1","","","",""
"J928","MCP23017 +3V3_SW solder pad","TestPoint:TestPoint_Pad_1.5x1.5mm","1","","","",""
"J929","MCP23017 GND solder pad","TestPoint:TestPoint_Pad_1.5x1.5mm","1","","","",""
"L1","4.7uH >=3A sat","Inductor_SMD:L_APV_ANR4020","1","","","https://www.digikey.com/en/products/result?keywords=4.7uH+%3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",""
"L2","4.7uH >=2A sat","Inductor_SMD:L_APV_ANR4020","1","","","https://www.digikey.com/en/products/result?keywords=4.7uH+%3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",""
"L3","1uH >=4A sat","Inductor_SMD:L_APV_ANR5040","1","","","https://www.digikey.com/en/products/result?keywords=1uH+%3E%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",""
"Q1","CSD83325L","Daughterboard:CSD83325L_YJE0006A","1","","","https://www.digikey.com/en/products/result?keywords=CSD83325L",""
"R1,R2","5.1k 1%","Resistor_SMD:R_0603_1608Metric","2","","","https://www.digikey.com/en/products/result?keywords=5.1k+1%2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",""
"R3","806R 1% ILIM","Resistor_SMD:R_0603_1608Metric","1","","","https://www.digikey.com/en/products/result?keywords=806+ohm+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",""
"R4","220R 1% CBSET","Resistor_SMD:R_0603_1608Metric","1","","","https://www.digikey.com/en/products/result?keywords=220+ohm+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",""
"R5","10k 1%","Resistor_SMD:R_0603_1608Metric","1","","","https://www.digikey.com/en/products/result?keywords=10k+1%25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",""
"R6,R7","2.2k","Resistor_SMD:R_0603_1608Metric","2","","","https://www.digikey.com/en/products/result?keywords=2.2k+Res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",""
"R8","523k 1%","Resistor_SMD:R_0603_1608Metric","1","","","https://www.digikey.com/en/products/result?keywords=523k+1%2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",""
"R9,R12","100k 1%","Resistor_SMD:R_0603_1608Metric","2","","","https://www.digikey.com/en/products/result?keywords=100k+1%2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",""
"R10,R13","100k","Resistor_SMD:R_0603_1608Metric","2","","","https://www.digikey.com/en/products/result?keywords=100k+Res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",""
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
